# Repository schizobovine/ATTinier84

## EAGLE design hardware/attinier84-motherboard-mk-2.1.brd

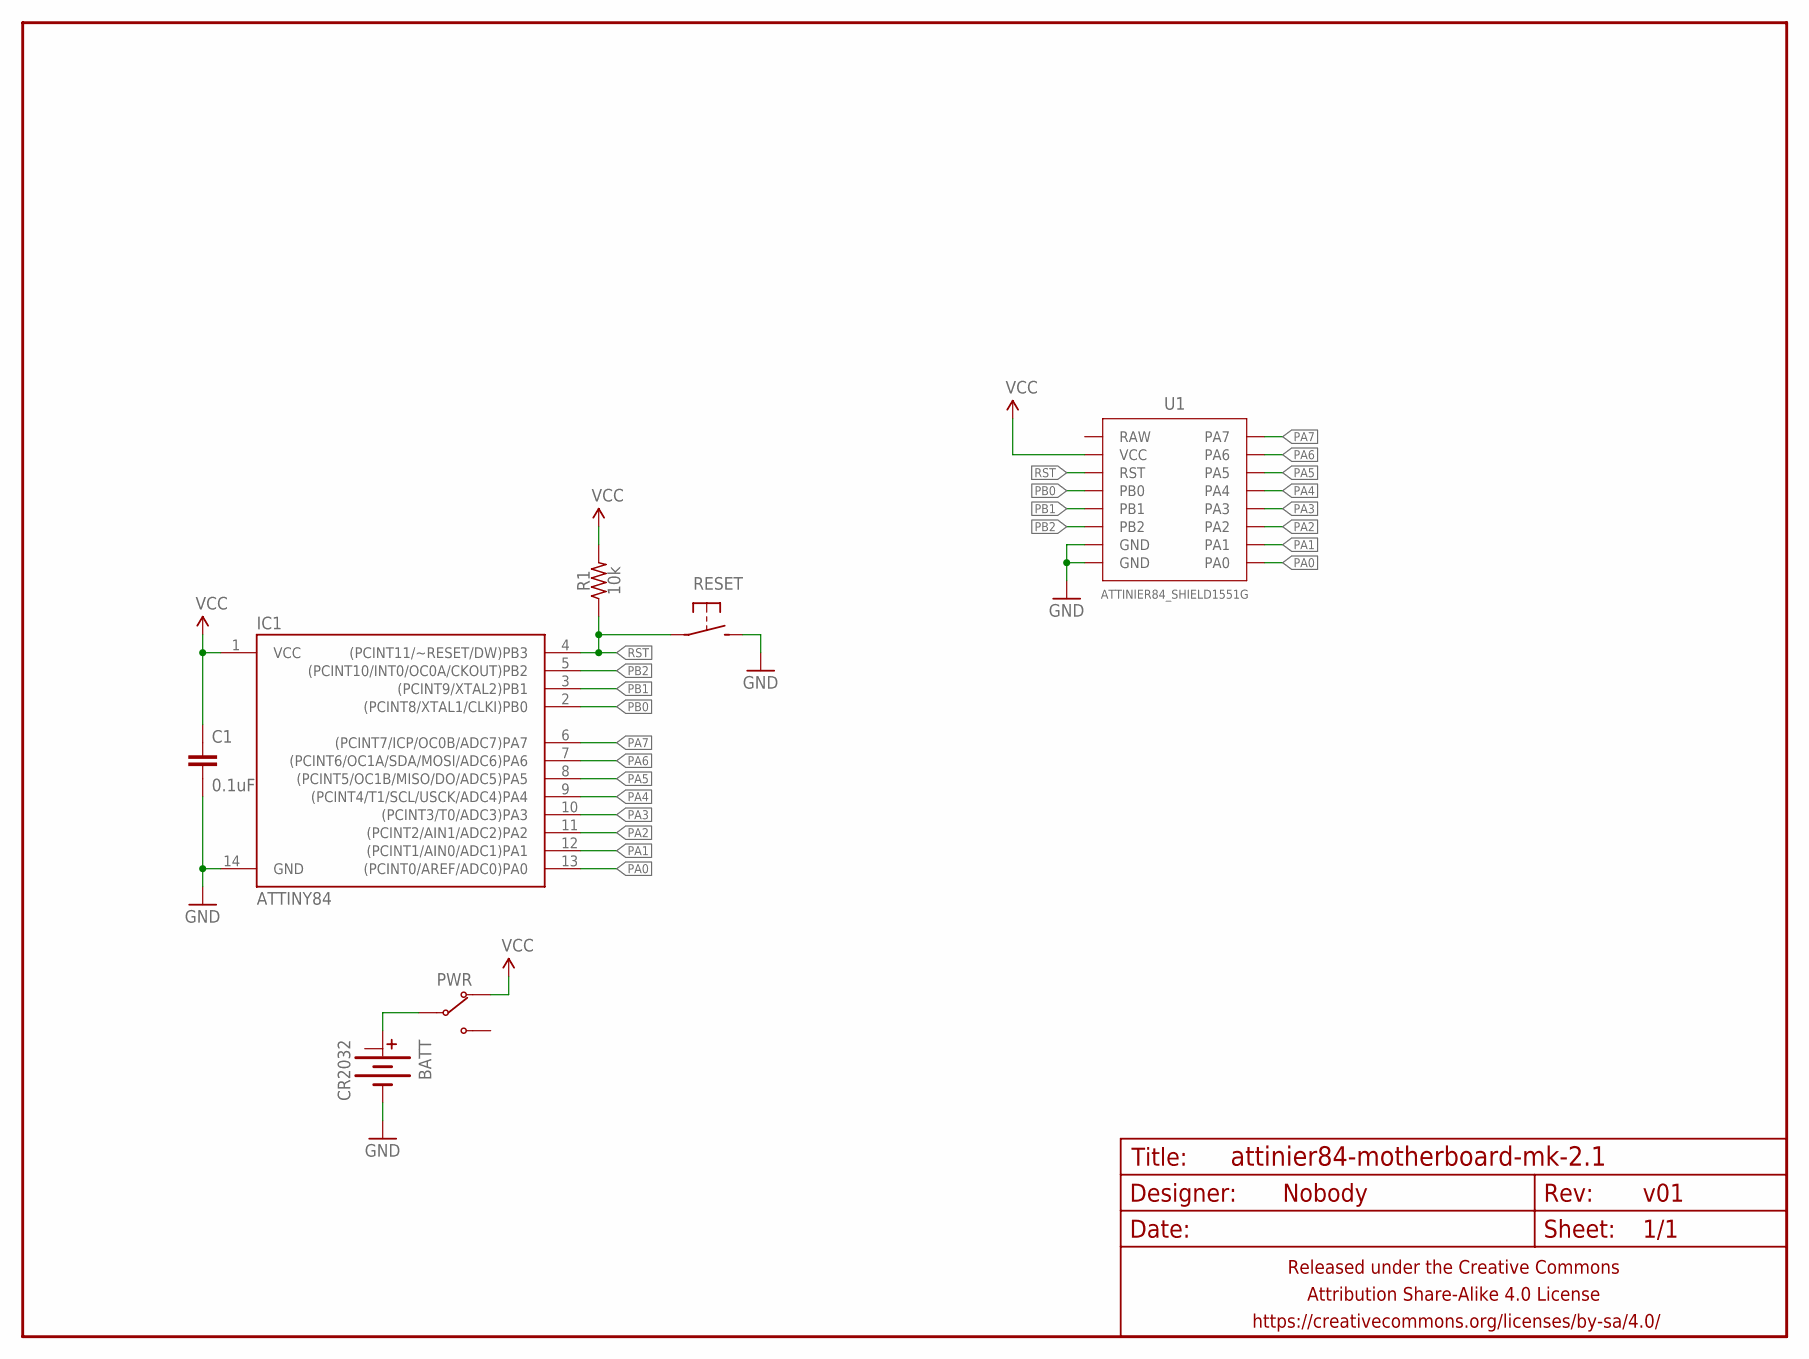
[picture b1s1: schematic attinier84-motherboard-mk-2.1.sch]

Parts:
BATT: CR2032; BATTCON_20MM_MINE
C1: 0.1uF; C0805
FRAME1: FRAME-LETTERNO_PACKAGE; DUMMY
IC1: ATTINY84; SO14
PWR: SWITCH-SPDTPTH-RA-2.54MM; SPDT-RA-2.54MM
R1: 10k; R0805
RESET: SPST-NO-TACT3MM-PTH-SMALL-PADS; DTS-3-SMALL-PADS
U1: ATTINIER84_SHIELD1551G; ATTINIER84_SHIELD2

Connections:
GND: BATT.BOTTOM (-), C1.2, IC1.14 (GND), RESET.2, U1.GND@1 (GND), U1.GND@2 (GND)
unnamed: BATT.TOP@1 (+), PWR.2 (COM)
PA0: IC1.13 ((PCINT0/AREF/ADC0)PA0), U1.PA0
PA1: IC1.12 ((PCINT1/AIN0/ADC1)PA1), U1.PA1
PA2: IC1.11 ((PCINT2/AIN1/ADC2)PA2), U1.PA2
PA3: IC1.10 ((PCINT3/T0/ADC3)PA3), U1.PA3
PA4: IC1.9 ((PCINT4/T1/SCL/USCK/ADC4)PA4), U1.PA4
PA5: IC1.8 ((PCINT5/OC1B/MISO/DO/ADC5)PA5), U1.PA5
PA6: IC1.7 ((PCINT6/OC1A/SDA/MOSI/ADC6)PA6), U1.PA6
PA7: IC1.6 ((PCINT7/ICP/OC0B/ADC7)PA7), U1.PA7
PB0: IC1.2 ((PCINT8/XTAL1/CLKI)PB0), U1.PB0
PB1: IC1.3 ((PCINT9/XTAL2)PB1), U1.PB1
PB2: IC1.5 ((PCINT10/INT0/OC0A/CKOUT)PB2), U1.PB2
RST: IC1.4 ((PCINT11/~RESET/DW)PB3), R1.1, RESET.1, U1.RST
VCC: C1.1, IC1.1 (VCC), PWR.1 (NC), R1.2, U1.VCC

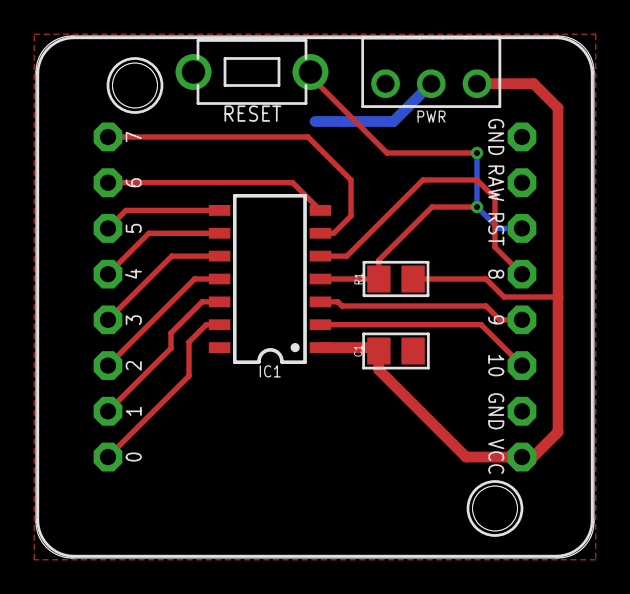
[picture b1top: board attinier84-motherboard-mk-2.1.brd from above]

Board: 2 copper layers, 31.0 x 29.0 mm, 8 parts (1 on the bottom side), 15 nets.

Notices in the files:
parts and their libraries:
A_butts: Released under the Creative Commons Attribution Share-Alike 4.0 License
A_butts: https://creativecommons.org/licenses/by-sa/4.0
A_butts: Released under the Creative Commons
